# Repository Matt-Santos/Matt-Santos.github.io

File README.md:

# Matt-Santos.github.io

This personal website is built with Jekyll and hosted on GitHub Pages, featuring a custom, responsive theme that is both lightweight and visually appealing. The design leverages modern HTML5 and CSS4 techniques for optimal browser compatibility, with minimal JavaScript (ie: [glightbox](https://biati-digital.github.io/glightbox/), [p5.js](https://p5js.org/), [KICanvas](https://github.com/theacodes/kicanvas)) used solely to enhance the user experience. Liquid is extensively employed for content management, automatically populating galleries, file listings, and project pages by pulling data from project repositories through a custom workflow. Additionally, all site settings and critical content are centralized in a config file, greatly streamlining the update process. The site also supports experimental browser based rendering of schematics, 3D models, and other dynamic content. The live version, serving as my personal portfolio, can be accessed [here](https://matt-santos.github.io/index). Suggestions for improvement are always welcome.

## Update Checklist

This list summarizes the content included in this repository that may require periodic updating. It should be reviewed in its entirety whenever major updates are performed to ensure completeness.

- [ ] [Contact Details](https://github.com/Matt-Santos/Matt-Santos.github.io/blob/main/_config.yml)
- [ ] [CV/Resume](https://github.com/Matt-Santos/Matt-Santos.github.io/blob/main/index.html)
	- [ ] [Print Versions](https://github.com/Matt-Santos/LaTeX-Workshop)
	- [ ] [Linkedin](https://www.linkedin.com/in/matthewjsantos)
	- [ ] [ORCID](https://orcid.org/0009-0006-1653-3882)
	- [ ] [Courses](https://github.com/Matt-Santos/Matt-Santos.github.io/blob/main/courses.html)
- [ ] [Extracurriculars](https://github.com/Matt-Santos/Matt-Santos.github.io/blob/main/extracurricular.html)
	- [ ] [Galleries](https://github.com/Matt-Santos/Matt-Santos.github.io/tree/main/assets/images/extracurricular)
- [ ] [Project Listing](https://github.com/Matt-Santos/Matt-Santos.github.io/blob/main/projects.html)
- [ ] [Archives](https://github.com/Matt-Santos/Matt-Santos.github.io/blob/main/archive.html)
- [ ] [Private GPG Key](https://github.com/Matt-Santos/Matt-Santos.github.io/blob/main/assets/files/msantos_public_key.asc)

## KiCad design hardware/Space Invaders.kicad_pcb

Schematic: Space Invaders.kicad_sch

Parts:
C1, C5: 0.1u; C_Disc_D3.8mm_W2.6mm_P2.50mm; Digikey 399-4151-ND
C2: 47n; C_Disc_D4.7mm_W2.5mm_P5.00mm; Digikey BC2686CT-ND
C3: 270u; CP_Radial_D8.0mm_P3.50mm; Digikey 493-5019-1-ND
C4: 330u; CP_Radial_D10.0mm_P5.00mm; Digikey 493-7053-1-ND
C6: 4700u; CP_Radial_D12.5mm_P5.00mm; Digikey 1189-1123-ND
D1: 1N5820; D_DO-201AD_P15.24mm_Horizontal; Digikey 1N5820-TPMSCT-ND
J1: ICSP Programing; PinHeader_1x05_P2.54mm_Vertical; Digikey WM19491-ND
J2: Main Connector; TerminalBlock_Phoenix_MKDS-3-11-5.08_1x11_P5.08mm_Horizontal; Digikey 277-1586-ND
L1: 190u; L_Axial_L9.5mm_D4.0mm_P15.24mm_Horizontal_Fastron_SMCC; Digikey 495-76015-1-ND
Q1, Q3, Q5, Q6: FQP30N06L; TO-220-3_Vertical; Digikey FQP30N06L-ND
Q2, Q4: 2N7000TACT; TO-92_Inline; Digikey 2N7000TACT-ND
R1, R4, R5, R6, R7, R8, R9, R10, R12: 10k; R_Axial_DIN0207_L6.3mm_D2.5mm_P10.16mm_Horizontal; Digikey 13-MFR50SFTE52-10KCT-ND
R2: 30k; R_Axial_DIN0207_L6.3mm_D2.5mm_P10.16mm_Horizontal; Digikey 13-MFR-25FTE52-30KCT-ND
R3: 3.6k; R_Axial_DIN0207_L6.3mm_D2.5mm_P10.16mm_Horizontal; Digikey 13-MFR-25FTE52-3K6CT-ND
R11: 68k; R_Axial_DIN0207_L6.3mm_D2.5mm_P10.16mm_Horizontal; Digikey 13-MFR-25FTE52-68KCT-ND
R13: 6.8k; R_Axial_DIN0207_L6.3mm_D2.5mm_P10.16mm_Horizontal; Digikey 13-MFR-25FRF52-6K8CT-ND
R14: 10k; Potentiometer_Bourns_3386P_Vertical; Digikey 3362R-103LF-ND
SYM1: Socket; Digikey AE9989-ND
SYM2: Socket; Digikey AE9986-ND
TP1: Jumper; TestPoint_THTPad_D3.0mm_Drill1.5mm
U1: PIC16F1705; DIP-14_W7.62mm; Digikey PIC16F1705-I/P-ND
U2: 24LC512-I/P; DIP-8_W7.62mm; Digikey 24LC512-I/P-ND
U3: LM386; DIP-8_W7.62mm; Digikey 296-44414-5-ND
U4: MC33167TVG; TO-220-5_Vertical; Digikey MC33167TVGOS-ND
U5: MC78M05CTG; TO-220-3_Vertical; Digikey MC78M05BTGOS-ND

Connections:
/5V: J1.2, R1.1, U1.1 (VDD), U2.8 (VCC), U3.6 (V+), U5.3 (VO)
/12V: C4.1, J2.11, U4.4, U5.1 (VI)
/A: J2.3, Q1.2 (D)
/A_Signal: Q1.1 (G), R4.2, U1.8 (C12IN2-/RC2)
/B: J2.4, Q3.2 (D)
/B_Signal: Q3.1 (G), R6.2, U1.7 (C12IN3-/RC3)
/C: J2.5, Q5.2 (D)
/C_Signal: Q5.1 (G), R9.2, U1.6 (C2OUT/RC4)
/D: J2.6, Q6.2 (D)
/D_Signal: Q6.1 (G), R10.2, U1.5 (RC5)
/Eyes: J2.8, Q2.1 (D)
/Eyes_Signal: Q2.2 (G), R5.2, U1.2 (RA5/T1CKI/OSC1/CLKIN)
/Flashers: J2.7, Q4.1 (D)
/Flashers_Signal: Q4.2 (G), R8.2, U1.3 (RA4/~T1G/OSC2/CLKOUT)
/GND: C4.2, C6.2, D1.2 (A), J1.3, J2.9, Q1.3 (S), Q2.3 (S), Q3.3 (S), Q4.3 (S), Q5.3 (S), Q6.3 (S), R3.2, R4.1, R5.1, R6.1, R7.2, R8.1, R9.1, R10.1, R14.1, U1.14 (VSS), U2.1 (A0), U2.2 (A1), U2.3 (A2), U2.4 (GND), U2.7 (WP), U3.2 (-), U3.4 (GND), U4.3, U5.2 (GND)
/MCLR: J1.1, R1.2, U1.4 (RA3/~MCLR/Vpp)
/PGC: J1.5, U1.12 (RA1/C12IN0-/ICSPCLK)
/PGD: J1.4, U1.13 (RA0/C1IN+/ICSPDAT)
/SCL: U1.10 (C2IN+/RC0), U2.6 (SCL)
/SDA: U1.9 (C12IN1-/RC1), U2.5 (SDA)
/Speaker: C3.1, J2.1
/Speaker_Signal: C1.1, U1.11 (RA2/T0CKI/INT/C1OUT)
/Vcc: C6.1, J2.10, L1.2, R13.1
/Volume: J2.2, R2.2, R3.1, TP1.1, U3.3 (+)
unnamed: C1.2, R2.1
unnamed: C2.1, R7.1
unnamed: C2.2, C3.2, U3.5
unnamed: C5.1, R11.2
unnamed: C5.2, U4.5
unnamed: D1.1 (K), L1.1, U4.1
unnamed: R11.1, R12.2, R13.2, U4.2
unnamed: R12.1, R14.2

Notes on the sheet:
Drops Load Voltage by 1.5V
8 Bayonet Bulbs Return Line
Pin 1 and 2 were reversed Inductor was in nH not uH
Socketed
Five 12V Pucks
MODIFY THE VOLUME RESISTOR ON HARNESS TO CONNECT TO GND INSTEAD OF 6.3V
5V to 8V adjustable @ 5A
8 Ohm 0.25W
Two Red LEDs Return with Builtin Resistor
I2C EEPROM
Speaker Amp, Gain = 20
10 KOhm Varriable Resistor -
Bayonet Drivers
Ring Light + & Steady Bayonet + & Volume Control Resistor +
Max 5A, Steady Puck Lights & LED Eyes + & Flashing Pucks +

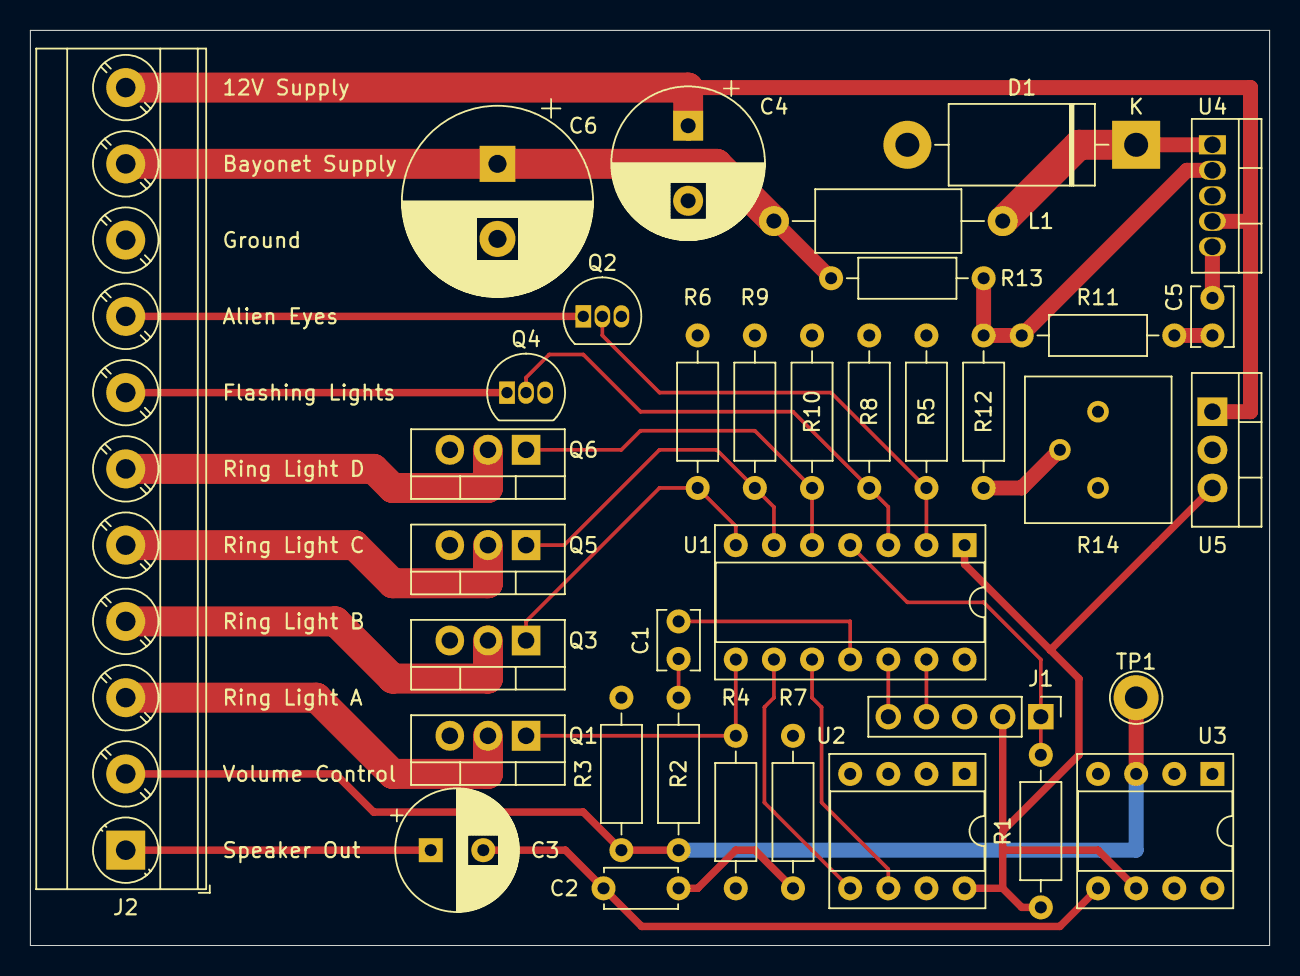
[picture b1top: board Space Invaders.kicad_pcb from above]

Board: 2 copper layers, 82.6 x 61.0 mm, 36 parts (0 on the bottom side), 32 nets.

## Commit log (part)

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2024-11-08 added index page with supporting media files
2024-11-08 remove IEEE Colabretec references
2024-11-09 completed skills section and performed minor fixes
2024-11-11 minor fixes to the index
2024-11-13 feat: modified format to support Jekyll compilation
2024-11-13 Fix: improper variable pass to include
2024-11-13 fix: image formatting and labels
2024-11-15 feat: add project page
2024-11-15 fix: liquid filter on project page
2024-11-15 fix: test ability to load markdown inside html
2024-11-15 feat: add extracurricular page
2024-11-15 fix: remove underline from markdownified Readmes
2024-11-15 fix: resized profile photo
2024-11-19 fix: scrollbar visibility
2024-11-21 feat: added document-verification post
2024-11-21 feat: added public gpg key to files
2024-11-23 feat: implement hidden blog
2024-11-23 fix: improve code css
2024-11-24 feat: add capstone project logo
2024-11-29 feat: restructured for project compatibility
2024-11-29 feat: add experimental css animation
2024-11-29 fix: project card image reference
2024-11-30 feat: improved extracurricular gallery
2024-11-30 fix: enable parallax effect on mobile
2024-11-30 fix: improve navbar readability
2024-12-01 feat: auto-generate project pages
2024-12-01 fix: formatting of project_card.html
2024-12-01 fix: update project layout
2024-12-01 feat: upgrade workflow to pull project files
2024-12-01 feat: add include for project gallery
2024-12-02 feat: add file list to project pages
2024-12-02 feat: create custom language bar
2024-12-02 feat: add dynamic toc to projects
2024-12-02 fix: filenames and minor format errors
2024-12-03 fix: project logo presence check
2024-12-03 fix: project overview centering with logo
2024-12-03 feat: add support for displaying project files
2024-12-03 feat: add ability to render schematics
2024-12-03 feat: transfer schematic render to lightbox
2024-12-04 feat: migrate to glightbox format
2024-12-04 Revert "feat: migrate to glightbox format"
    This reverts commit 49d7a36083b618bb70fd0383947ec993ff8a9f8e.
2024-12-04 Revert "feat: transfer schematic render to lightbox"
    This reverts commit a29bd8e7ffdf32e7c38cc11b03fada3bd7ce72f1.
2024-12-04 Reapply "feat: transfer schematic render to lightbox"
    This reverts commit dba4d0abb4c589b0989de6d5b3f2257177379656.
2024-12-04 Reapply "feat: migrate to glightbox format"
    This reverts commit ad53d569138ed16c261a54c0802c576a68e38262.
2024-12-04 fix: re-enable glightbox
2024-12-04 feat: enable kicad rendering with glightbox
2024-12-04 fix: cleanup glightbox formating
2024-12-04 fix: css "before" conflict
2024-12-04 fix: lightbox css style issues
2024-12-04 fix: enlarge schematic render size
2024-12-04 feat: implement embedded stl viewer
2024-12-04 feat: integrate BOM view into glightbox
2024-12-04 fix: parallax effect for IOS
2024-12-04 feat: improved compatibility for parallax
2024-12-05 fix: remove temp testing files
2024-12-05 feat: add background circuit effect
2024-12-05 fix: add missing cv image
2024-12-05 fix: suppress console debug messages
2024-12-10 fix: project page labeling
2024-12-12 fix: update extracurricular gallery
2024-12-12 feat: added experiment images to gallery
2024-12-13 feat: add minimal dark mode, resolves #2
2024-12-13 Revert "feat: add minimal dark mode, resolves #2"
    This reverts commit 726ad92ed8fc9e17b6825ac57bc6a1ef19535a71.
2024-12-13 Reapply "feat: add minimal dark mode, resolves #2"
    This reverts commit 1a7576b10eb570ecb0ce06abc275000b87b075f2.
2024-12-13 fix: correct pointer events on canvas
2024-12-13 feat: observe user theme preferences + remember
2024-12-13 feat: update extracurricular section
2024-12-14 fix: optimized all images
2024-12-14 fix: lightbox load priority error
2024-12-21 fix: macOS z-index test
2024-12-21 fix: make overlay static which resolves #7
2024-12-21 fix: convert overlay to progressive jpg
2024-12-22 fix: update project formatting to jpg
2024-12-23 fix: change nested href to overlay
2024-12-23 fix: project card on small screens resolves #3
2024-12-26 fix: access private repo data
2025-01-10 feat: update cv section
2025-01-10 fix: add support for spaces in filenames
2025-01-11 fix: image header label wrap
2025-07-03 fix: updated CV links/references
2025-07-03 fix: update graduate courses list
2025-07-03 fix: CV project name
2025-07-05 fix: minor spelling mistake
